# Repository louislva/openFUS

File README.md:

# openFUS: a cheap, open-source, easy to replicate FUS device for hackers & researchers

View [current design (subject to change)](/design/) 

### Background

Transcranial focused ultrasound (tFUS) is a non-invasive neuromodulation technique, which has millimeter precision and can reach any depth in the brain. It's safe, and has been used in humans to:

- [improve mood](https://www.frontiersin.org/articles/10.3389/fnhum.2020.00052)
- [reduce sensitivity to pain](https://www.jneurosci.org/content/44/8/e1011232023) (and [again](https://www.sciencedirect.com/science/article/pii/S1935861X20302746))
- [decrease amygdala activity (for treating anxiety)](<https://www.brainstimjrnl.com/article/S1935-861X(24)00040-8/fulltext>)

It's incredible that we have a **non-invasive** way to do the equivalent of putting a wire _anywhere_ in the brain and stimulating it. Why isn't this everywhere?

1. tFUS is relatively new & underdeveloped. It's quickly gaining steam (see [Prophetic](https://x.com/PropheticAI), etc.), but good human studies really only started coming out in the late 2010s!
2. It's still niche in academia, and the hardware is expensive. This means relatively few labs can do it.
3. No good treatment protocols, which makes effect sizes sub-therapeutic. We have the tool but we don't quite know how to use it (sonication parameters, environment, sequence / repetitions, etc.)

### How tFUS works

You wouldn't expect ultrasound could modulate the brain — electric currents or magnetic fields, sure, but acoustic waves? Apparently yes! The mechanisms are still unknown, but by changing the parameters of the ultrasound pulses, you can control whether you get a net excitatory or inhibitory effect.

Then, in order to get the ultrasound to the right part of the brain, you need to focus it. This can be done in many ways, but the easiest to illustrate, is if you have a bunch of weak ultrasound beams, which all converge at the same point:

The beam will be too weak to do anything at the surface, but at the focal point, it will be strong enough to affect neurons.

### Motivation for **openFUS**

Let's compare tFUS to EEG. Nowadays, every neuroscience _undergrad_ is working with EEG (because [OpenBCI](https://openbci.com/) sells $1000 EEGs). Even hackers and psychonauts can use it to make discoveries (for example, [Jhourney](https://x.com/stephen_zerfas/status/1755149844921057744) finding neural correlates of the 2nd jhana).

We've not reached this moment with tFUS yet, but when we do, it's gonna lead to [an explosion in neuroscience](https://sarahconstantin.substack.com/p/testing-human-augmentation) since we can easily and rapidly test hypotheses. Sonicate one area, give a subjective report, take an fMRI, repeat.

For this neuroscience renaissance to happen, **FUS needs to be more accessible**. We need an open-source starting point for engineers to build on top of, and independent researchers to buy and use.

**North star:** make a device theoretically capable of replicating ["Transcranial Focused Ultrasound to the Right Prefrontal Cortex Improves Mood and Alters Functional Connectivity in Humans"](https://www.frontiersin.org/articles/10.3389/fnhum.2020.00052), for less than $1k.

### Contributing

We need your help! Here are some things you can help out with:

- Great software (for neuronavigation, setting sonication params, self-blinding, peer-to-peer science, etc.)
- Great product design (for the handheld device itself)
- Driving electronics (e.g. amplify to generate LOTS of power as cheap as possible)
- Funding (we're not spending any time fundraising, but if you can wire cash with low overhead, it'd help a lot)

If you're interested in contributing, please reach out to Louis Arge [on Twitter](https://x.com/louisvarge), [by email](mailto:louis@muditalabs.ai), or if you have something very concrete: just open a PR.

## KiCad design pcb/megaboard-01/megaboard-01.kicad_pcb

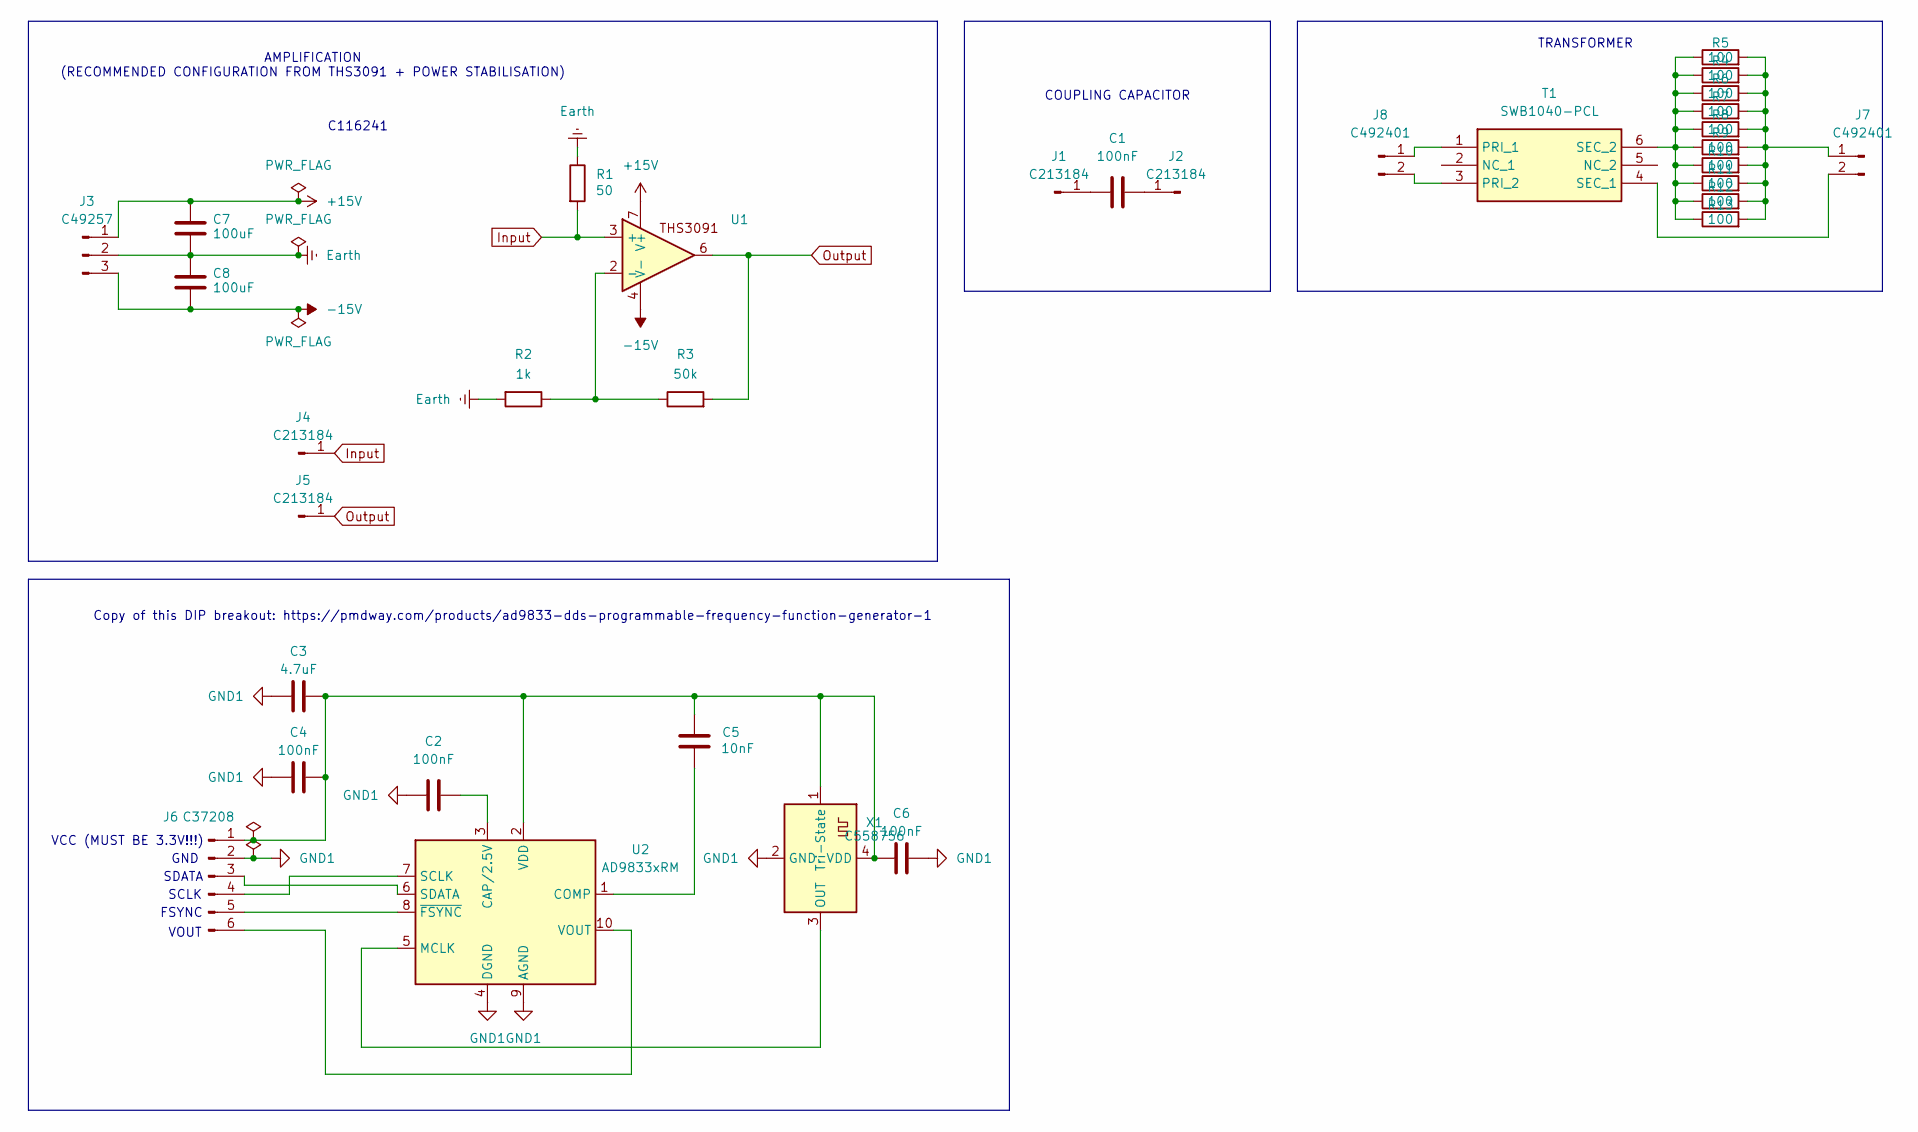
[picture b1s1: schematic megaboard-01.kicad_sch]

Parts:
C1, C2, C4, C6: C14663; C_0603_1608Metric
C3: C1779; C_0805_2012Metric
C5: C57112; C_0603_1608Metric
C7, C8: C116241; CP_Elec_8x10
J1, J2, J4, J5: C213184; PinHeader_1x01_P2.54mm_Vertical
J3: C49257; PinHeader_1x03_P2.54mm_Vertical
J6: C37208; PinHeader_1x06_P2.54mm_Vertical
J7, J8: C492401; PinHeader_1x02_P2.54mm_Vertical
R1: C849792; R_0603_1608Metric
R2: C21190; R_0603_1608Metric
R3: C166559; R_0402_1005Metric
R4, R5, R6, R7, R8, R9, R10, R11, R12, R13: C17901; R_1206_3216Metric
T1: SWB1040-PCL; SWB1040PCL; Mouser Part Number 994-SWB1040-PCL
U1: THS3091DDAR; TI_SO-PowerPAD-8_ThermalVias
U2: AD9833xRM; MSOP-10_3x3mm_P0.5mm
X1: C558756; Crystal_SMD_7050-4Pin_7.0x5.0mm

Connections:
+15V: C7.1, J3.1, U1.7 (V+)
-15V: C8.2, J3.3, U1.4 (V-)
Earth: C7.2, C8.1, J3.2, R1.1, R2.2
GND1: C2.1, C3.1, C4.1, C6.2, J6.2, U2.4 (DGND), U2.9 (AGND), X1.2 (GND)
Input: J4.1, R1.2, U1.3 (+)
unnamed: C1.1, J1.1
unnamed: C1.2, J2.1
unnamed: C3.2, C4.2, C5.1, C6.1, J6.1, U2.2 (VDD), X1.1 (Tri-State), X1.4 (VDD)
unnamed: J6.3, U2.6 (SDATA)
unnamed: J6.4, U2.7 (SCLK)
unnamed: J6.5, U2.8 (~FSYNC)
unnamed: J6.6, U2.10 (VOUT)
unnamed: J7.1, R4.2, R5.2, R6.2, R7.2, R8.2, R9.2, R10.2, R11.2, R12.2, R13.2
unnamed: J7.2, T1.4 (SEC_1)
unnamed: J8.1, T1.1 (PRI_1)
unnamed: J8.2, T1.3 (PRI_2)
unnamed: R4.1, R5.1, R6.1, R7.1, R8.1, R9.1, R10.1, R11.1, R12.1, R13.1, T1.6 (SEC_2)
unnamed: R2.1, R3.1, U1.2 (-)
unnamed: C2.2, U2.3 (CAP/2.5V)
unnamed: C5.2, U2.1 (COMP)
unnamed: U2.5 (MCLK), X1.3 (OUT)
Output: J5.1, R3.2, U1.6

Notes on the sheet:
Copy of this DIP breakout: https://pmdway.com/products/ad9833-dds-programmable-frequency-function-generator-1
SDATA
VCC (MUST BE 3.3V!!!)
C116241
FSYNC
SCLK
VOUT
AMPLIFICATION (RECOMMENDED CONFIGURATION FROM THS3091 + POWER STABILISATION)
COUPLING CAPACITOR
GND
TRANSFORMER

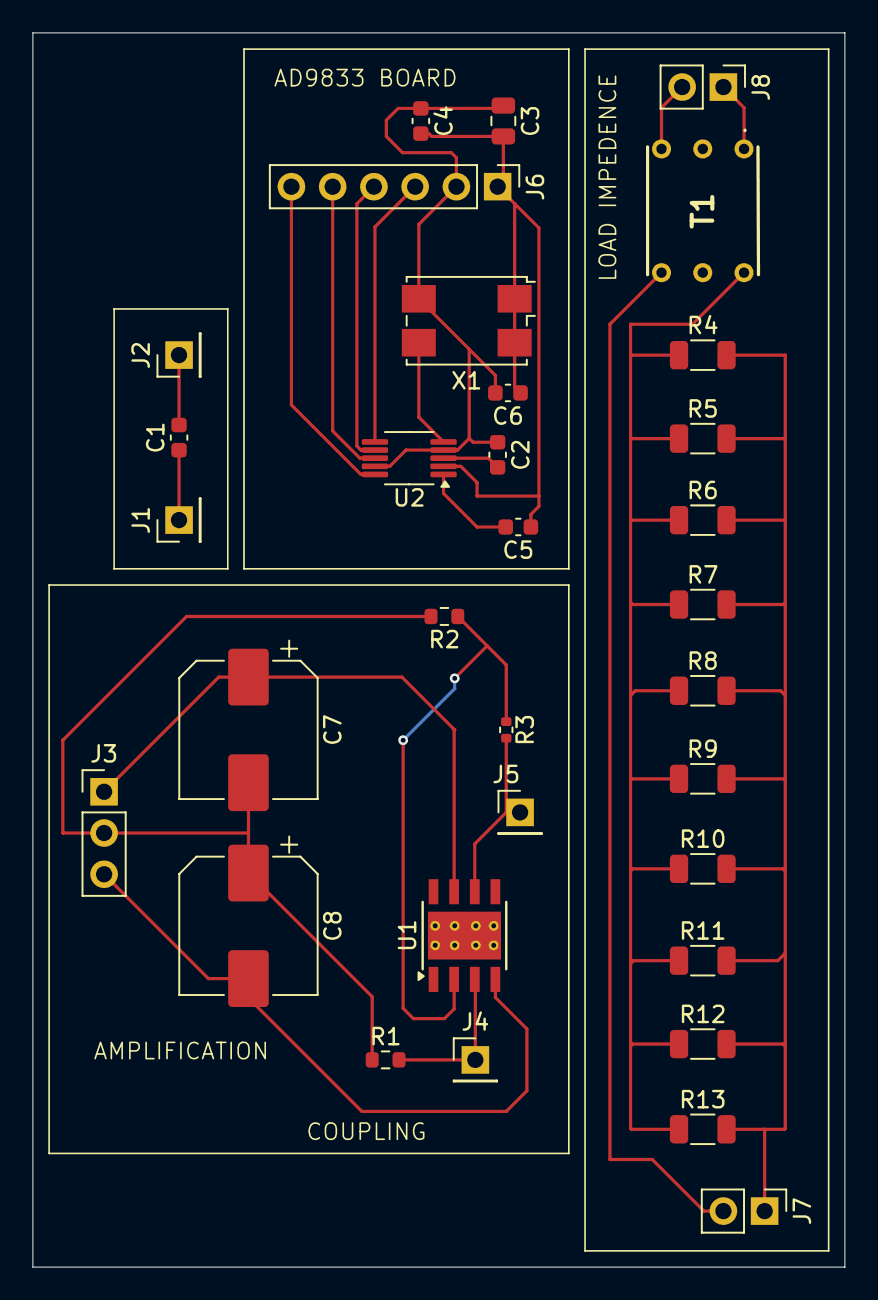
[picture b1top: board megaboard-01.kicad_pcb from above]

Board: 2 copper layers, 50.0 x 76.0 mm, 33 parts (0 on the bottom side), 22 nets.

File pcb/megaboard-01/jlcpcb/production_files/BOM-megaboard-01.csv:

Comment,Designator,Footprint,LCSC
C116241,"C7,C8",CP_Elec_8x10,C116241
C14663,"C1,C2,C4,C6",C_0603_1608Metric,C14663
AD9833xRM,U2,MSOP-10_3x3mm_P0.5mm,C1519069
RTT025002FTH,R3,R_0402_1005Metric,C166559
C1779,C3,C_0805_2012Metric,C1779
C17901,"R10,R11,R12,R13,R4,R5,R6,R7,R8,R9",R_1206_3216Metric,C17901
THS3091DDAR,U1,TI_SO-PowerPAD-8_ThermalVias,C181226
0603WAF1001T5E,R2,R_0603_1608Metric,C21190
Conn_01x01_Pin,"J1,J2,J4,J5",PinHeader_1x01_P2.54mm_Vertical,C213184
C37208,J6,PinHeader_1x06_P2.54mm_Vertical,C37208
C492401,"J7,J8",PinHeader_1x02_P2.54mm_Vertical,C492401
Conn_01x03_Pin,J3,PinHeader_1x03_P2.54mm_Vertical,C49257
C558756,X1,Crystal_SMD_7050-4Pin_7.0x5.0mm,C558756
C57112,C5,C_0603_1608Metric,C57112
RT0603BRE0750RL,R1,R_0603_1608Metric,C849792
SWB1040-PCL,T1,SWB1040PCL,

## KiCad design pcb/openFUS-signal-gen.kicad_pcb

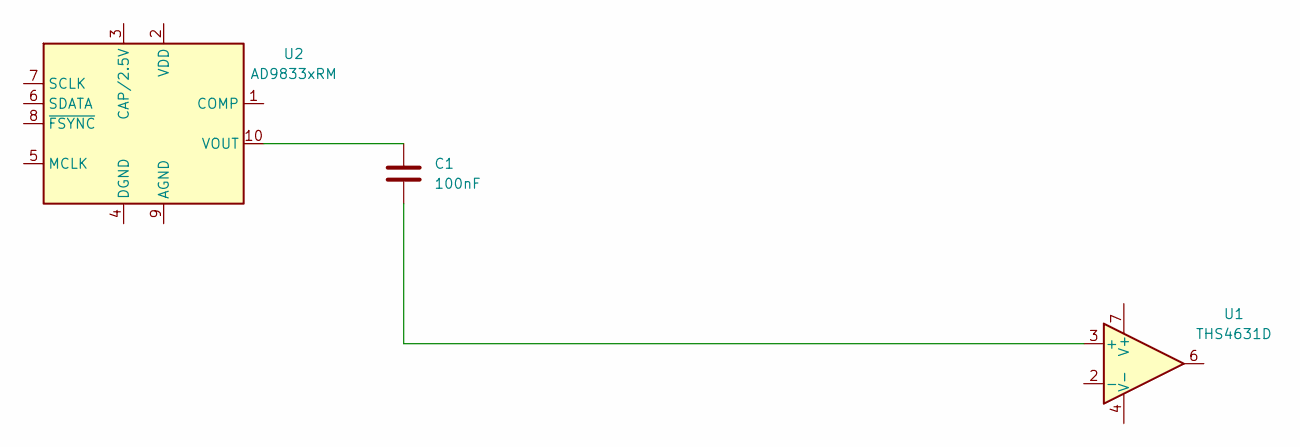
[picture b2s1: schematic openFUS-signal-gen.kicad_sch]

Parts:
C1: 100nF; C_Axial_L3.8mm_D2.6mm_P7.50mm_Horizontal
U1: THS4631D; SOIC-8_3.9x4.9mm_P1.27mm
U2: AD9833xRM; MSOP-10_3x3mm_P0.5mm

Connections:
unnamed: C1.2, U1.3 (+)
unnamed: C1.1, U2.10 (VOUT)

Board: 2 copper layers, 3 parts (0 on the bottom side), 2 nets, no tracks yet.

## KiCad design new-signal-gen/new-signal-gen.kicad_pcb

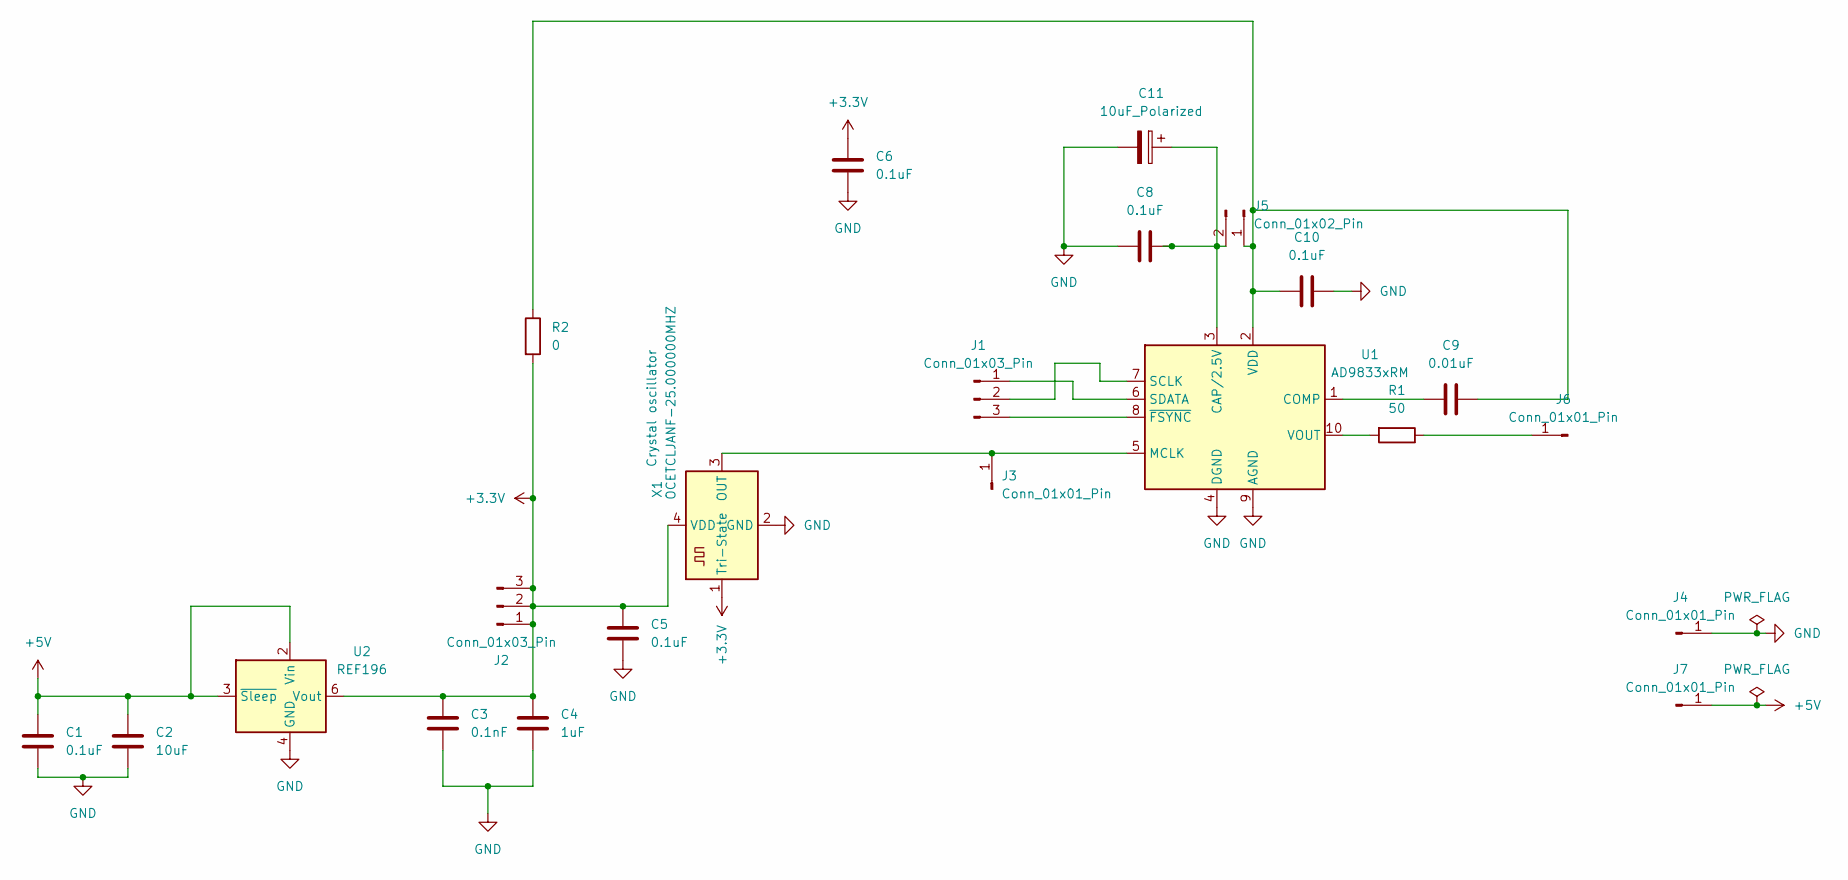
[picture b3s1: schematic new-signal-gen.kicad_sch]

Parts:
C1, C5, C6, C8, C10: 0.1uF; C_0805_2012Metric
C2: 10uF; C_1206_3216Metric
C3: 0.1nF; C_0805_2012Metric
C4: 1uF; C_0402_1005Metric
C9: 0.01uF; C_1206_3216Metric
C11: 10uF_Polarized; CP_Elec_5x5.4
J1, J2: Conn_01x03_Pin; PinHeader_1x03_P2.54mm_Vertical
J3, J4, J6, J7: Conn_01x01_Pin; PinHeader_1x01_P2.54mm_Vertical
J5: Conn_01x02_Pin; PinHeader_1x02_P2.54mm_Vertical
R1: 50; R_0402_1005Metric
R2: 0; R_2512_6332Metric
U1: AD9833xRM; MSOP-10_3x3mm_P0.5mm
U2: REF196; SOIC-8_3.9x4.9mm_P1.27mm
X1: OCETCLJANF-25.000000MHZ; Crystal_SMD_7050-4Pin_7.0x5.0mm

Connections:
+3.3V: C3.1, C4.1, C5.1, C6.1, J2.1, J2.2, J2.3, R2.2, U2.6 (Vout), X1.1 (Tri-State), X1.4 (VDD)
+5V: C1.1, C2.1, J7.1, U2.2 (Vin), U2.3 (~Sleep)
GND: C1.2, C2.2, C3.2, C4.2, C5.2, C6.2, C8.1, C10.2, C11.2, J4.1, U1.4 (DGND), U1.9 (AGND), U2.4 (GND), X1.2 (GND)
unnamed: J1.1, U1.6 (SDATA)
unnamed: J1.2, U1.7 (SCLK)
unnamed: J1.3, U1.8 (~FSYNC)
unnamed: J3.1, U1.5 (MCLK), X1.3 (OUT)
unnamed: C9.2, C10.1, J5.1, R2.1, U1.2 (VDD)
unnamed: C8.2, C11.1, J5.2, U1.3 (CAP/2.5V)
unnamed: J6.1, R1.1
unnamed: C9.1, U1.1 (COMP)
unnamed: R1.2, U1.10 (VOUT)

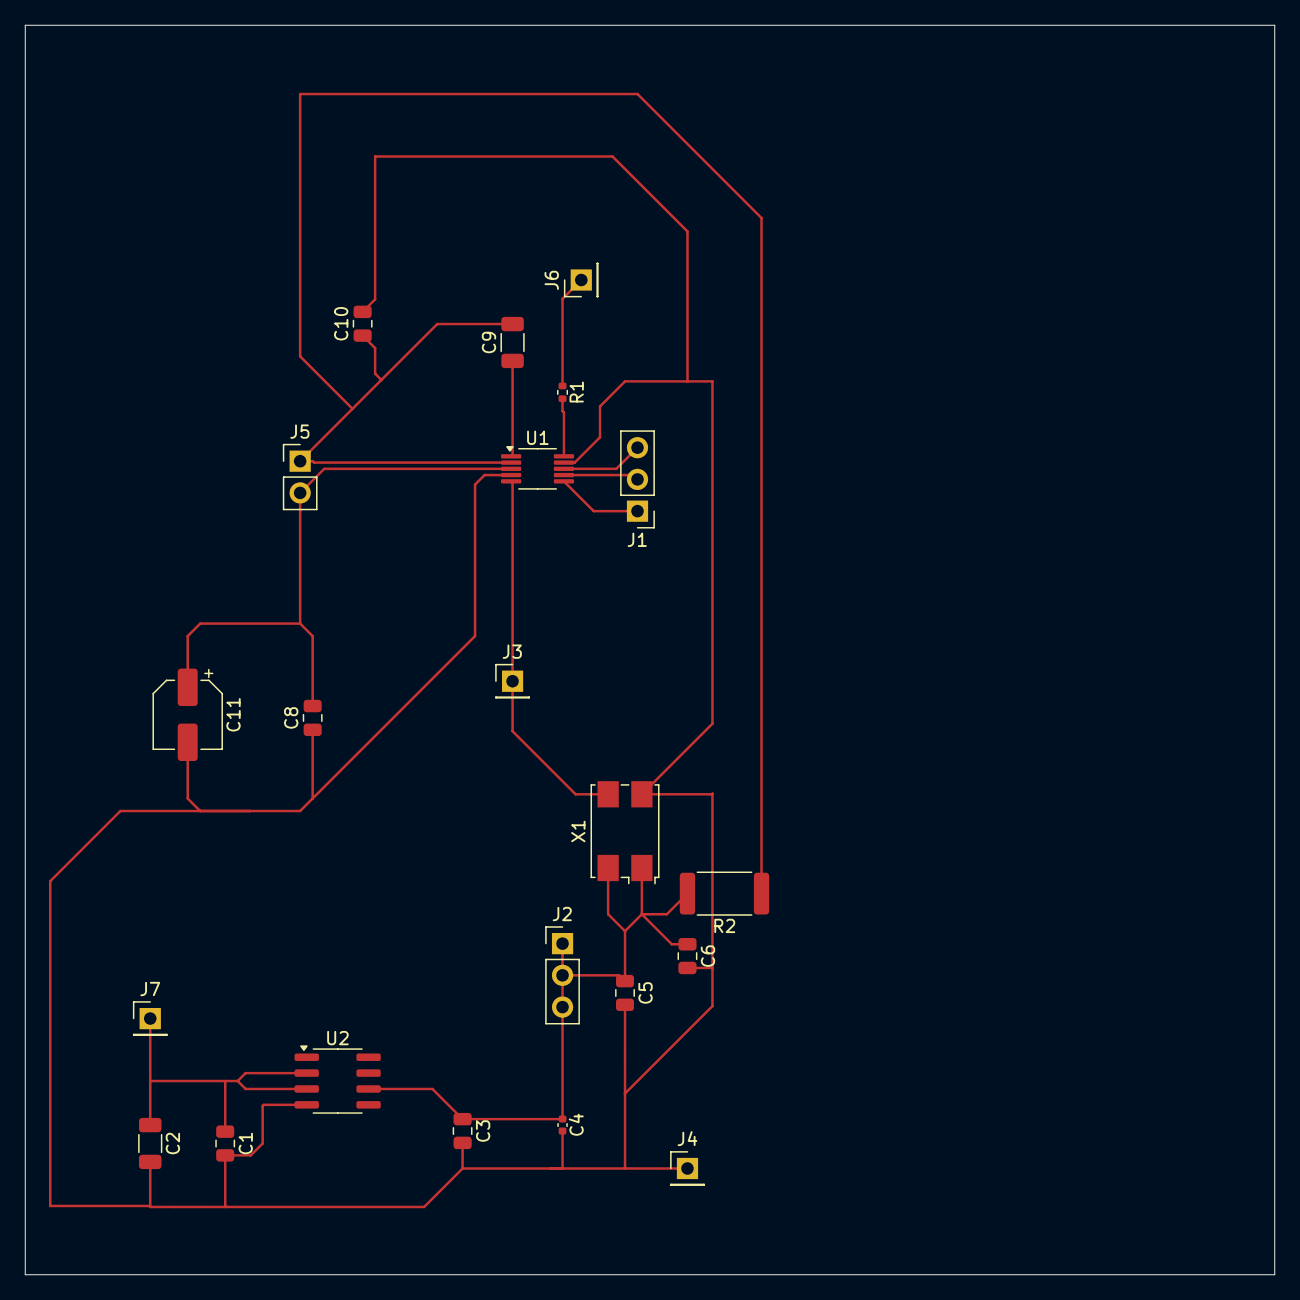
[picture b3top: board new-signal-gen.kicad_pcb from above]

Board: 2 copper layers, 100.0 x 100.0 mm, 22 parts (0 on the bottom side), 12 nets.

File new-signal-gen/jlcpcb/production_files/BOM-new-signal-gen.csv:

Comment,Designator,Footprint,LCSC
Conn_01x02_Pin,J5,PinHeader_1x02_P2.54mm_Vertical,C124375
1uF,C4,C_0402_1005Metric,C14445
0.1uF,"C1,C10,C5,C6,C8",C_0805_2012Metric,C1711
0,R2,R_2512_6332Metric,C25469
10uF_Polarized,C11,CP_Elec_5x5.4,C4747971
10uF,C2,C_1206_3216Metric,C47971
Conn_01x03_Pin,"J1,J2",PinHeader_1x03_P2.54mm_Vertical,C49257
OCETCLJANF-25.000000MHZ,X1,Crystal_SMD_7050-4Pin_7.0x5.0mm,C558756
50,R1,R_0402_1005Metric,C60490
REF196,U2,SOIC-8_3.9x4.9mm_P1.27mm,C70012
Conn_01x01_Pin,"J3,J4,J6,J7",PinHeader_1x01_P2.54mm_Vertical,C81276
0.1nF,C3,C_0805_2012Metric,C82028
0.01uF,C9,C_1206_3216Metric,C9194
AD9833xRM,U1,MSOP-10_3x3mm_P0.5mm,C9652

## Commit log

2024-06-26 copied blog post I once wrote into README
2024-06-26 really ugly make_lens.py script, but it works
2024-06-26 misc changes
2024-06-28 Word vomit
2024-06-28 fix wording
2024-06-28 don't like uppercase
2024-06-28 wrote down timelines
2024-06-28 Some good docs!
2024-07-01 premade link
2024-07-02 Some more docs
2024-07-02 better
2024-07-03 better (can't remember what I made lol)
2024-07-03 fixes
2024-07-03 blender file
2024-07-03 render
2024-07-04 switch from PMP to PP
2024-07-04 Update design doc
2024-07-04 Better todo
2024-07-04 lens cad
2024-07-04 add padding
2024-07-04 rename to lens!
2024-07-04 ignore
2024-07-04 we switch to cad software
2024-07-04 Padding
2024-07-04 github social preview
2024-07-05 Rough BOM + reorganization
2024-07-05 reverse engineer silver epoxy
2024-07-05 reverse engineer different silver epoxy's
2024-07-06 fix social preview bug
2024-07-08 got opamp circuit wokring at least, let's lock that in
2024-07-08 some notes, unfinished, committing for safety
2024-07-08 ignore noisy LTSpice stuff
2024-07-09 stuff
2024-07-09 driver circuit with actual amplification ???
2024-07-09 more cool stuff
2024-07-10 more managable level of resistance
2024-07-10 trasnformer simulation
2024-07-10 just do 100nF fuck it
2024-07-10 save pzt materials list from steminc
2024-07-10 more power!
2024-07-14 matlab thingy
2024-07-15 obsacle
2024-07-15 load 3d lens kind of
2024-07-15 something good
2024-07-15 think this is roughly righr
2024-07-15 hahaha
2024-07-15 put lens in scene
2024-07-15 good very good
2024-07-15 rename
2024-07-15 BUT WHERE DOES SOURCE COME FROM
2024-07-15 it looks happy now
2024-07-15 todo fix
2024-07-15 fix stuff! it works omg omg omg so happy
2024-07-15 record at many spots
2024-07-15 better axis and centering
2024-07-15 measure from end of lens
2024-07-16 stuff ig
2024-07-16 soldering is hard
2024-07-16 remove shopping list
2024-07-16 Clean up
2024-07-16 Link simulation
2024-07-17 script
2024-07-17 tool to search difference piezoceramics for sale
2024-07-18 cleaned
2024-07-21 various stuff
2024-07-23 more like reality
2024-07-25 playing with aruco
2024-07-25 it works!
2024-07-25 tiny bit of housekeeping
2024-07-25 We can do measurements
2024-07-25 Better impedence matching doc
2024-07-25 revert more power
2024-07-25 Transformers
2024-07-25 neuronav ideas
2024-07-26 can't even remember what i did here
2024-07-26 change density to agree more with other people's measurements of MG epoxies
2024-08-02 implementation of recommended circuit from data sheet of THS3091
2024-08-02 MEGABOARD
2024-08-09 lots of case stuff
2024-08-11 change megaboard
2024-08-11 commit all the kicad stuff for orderliness
2024-08-11 gitignore some more
2024-08-11 move all pcb into pcb folder
2024-08-11 more order
2024-08-11 cad-outputs -> cad/outputs
2024-08-11 clean up in neuronav folder
2024-08-11 ltspice
2024-08-11 render/
2024-08-11 commit CAD models
2024-08-11 small design/ changes
2024-08-11 Ignore all outputs
2024-08-25 Git commit
2024-08-25 Calc
2024-08-26 todos
2024-08-28 updates to case
2024-08-29 some stupid shit
2024-08-29 fresnel lens!
2024-08-29 fix fresnel mold
2024-09-27 make stuff happen
2024-09-27 slice anything
2024-09-27 add mesh
2024-09-27 thingy
2024-09-27 whhatever
2024-10-02 wtf was i doing
2024-10-02 end to end type
2024-10-02 correct axis ig
2024-10-02 translation in millimeters
2024-10-02 rolling avg
2024-10-02 outlier
2024-10-02 smooth sines and cosines i think maybe
2024-10-02 readme fix
